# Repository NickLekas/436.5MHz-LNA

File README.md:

# 436.5MHz-LNA
A JFET common gate LNA for 436.5MHz

This is untested and may not work as designed.

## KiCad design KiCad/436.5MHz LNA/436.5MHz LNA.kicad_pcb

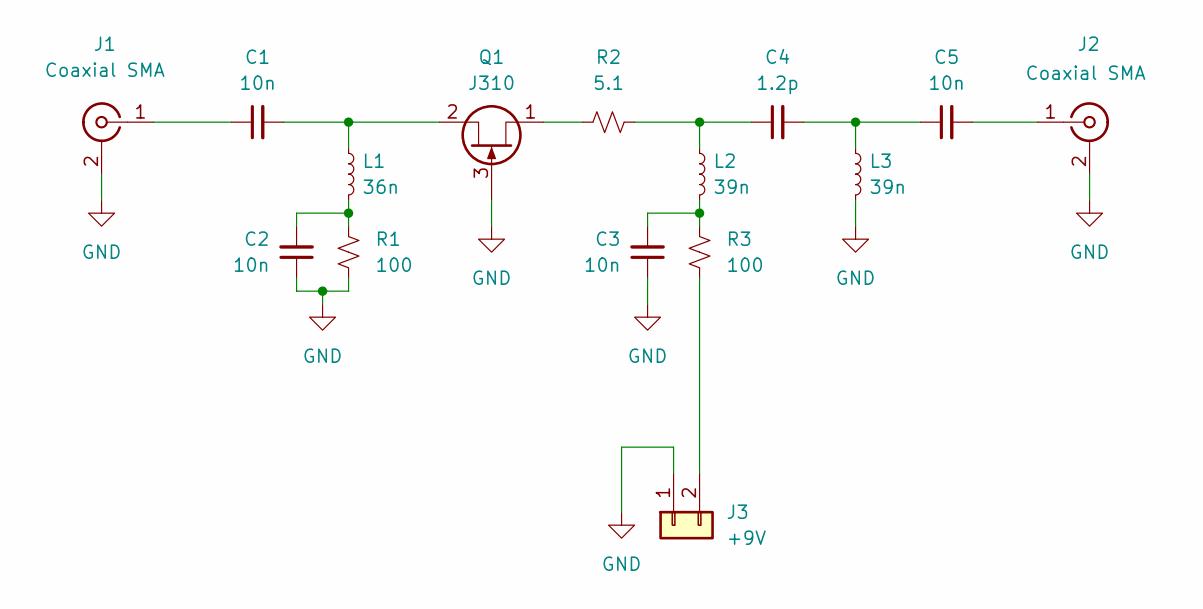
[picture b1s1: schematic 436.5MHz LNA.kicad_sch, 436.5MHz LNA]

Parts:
C1, C2, C3, C5: 10n; C_0603_1608Metric; MPN CL10C102JB8NNNC
C4: 1.2p; C_0603_1608Metric; MPN CC0603BRNPO9BN1R2‎
J1, J2: Coaxial SMA; SMA_Amphenol_132289_EdgeMount; MPN BU-1420701801
J3: +9V; PinHeader_1x02_P2.54mm_Vertical
L1: 36n; L_0603_1608Metric; MPN 0603DC-36NXJRW
L2, L3: 39n; L_0603_1608Metric; MPN 0603DC-39NXJRW
Q1: J310; SOT-23; MPN MMBFJ310LT3G
R1, R3: 100; R_0603_1608Metric; MPN CRGCQ0603F100R
R2: 5.1; R_0603_1608Metric; MPN RC0603FR-075R1L

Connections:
GND: C2.1, C3.1, J1.2 (Ext), J2.2 (Ext), J3.1, L3.2, Q1.3 (G), R1.2
unnamed: C1.1, J1.1 (In)
unnamed: C1.2, L1.1, Q1.2 (S)
unnamed: C2.2, L1.2, R1.1
unnamed: C3.2, L2.2, R3.1
unnamed: C4.1, L2.1, R2.2
unnamed: C4.2, C5.1, L3.1
unnamed: C5.2, J2.1 (In)
unnamed: J3.2, R3.2
unnamed: Q1.1 (D), R2.1

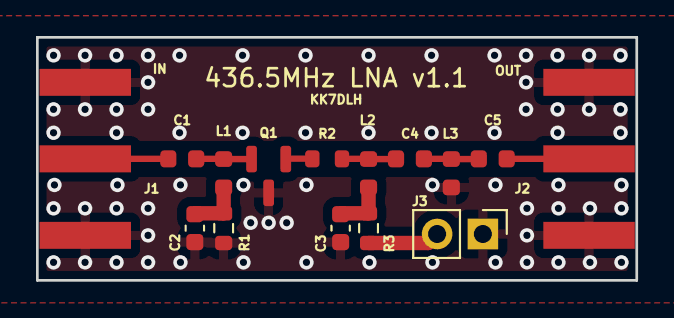
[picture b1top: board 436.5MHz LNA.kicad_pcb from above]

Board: 2 copper layers, 33.3 x 13.5 mm, 15 parts (0 on the bottom side), 10 nets.

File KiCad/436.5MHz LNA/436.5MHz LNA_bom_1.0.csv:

Quantity Per PCB,References,Value,MFN,MPN,Footprint,Dist,DPN,Datasheet
1,C4,1.2p,YAGEO,CC0603BRNPO9BN1R2‎,C_0603_1608Metric,DigiKey,311-3825-1-ND‎,~
4,C1 C2 C3 C5,10n,Samsung Electro-Mechanics,CL10C102JB8NNNC,C_0603_1608Metric,DigiKey,1276-1091-2-ND,~
1,J3,+9V,,,PinHeader_1x02_P2.54mm_Vertical,DigiKey,,~
2,J1 J2,Coaxial SMA,Muller Electric Co,BU-1420701801,SMA_Amphenol_132289_EdgeMount,DigiKey,314-1702-ND‎,https://www.muellerelectric.com/product_files/785/DS-BU-1420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
1,L1,36n,Coilcraft,0603DC-36NXJRW,L_0603_1608Metric,Coilcraft,0603DC-36NXJRW,https://www.coilcraft.com/getmedia/f3d98f97-cbe2-41fa-b3a9-5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
2,L2 L3,39n,Coilcraft,0603DC-39NXJRW,L_0603_1608Metric,Coilcraft,0603DC-39NXJRW,https://www.coilcraft.com/getmedia/f3d98f97-cbe2-41fa-b3a9-5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
1,Q1,J310,OnSemi,MMBFJ310LT3G,SOT-23,DigiKey,MMBFJ310LT3GOSCT-ND‎,https://www.farnell.com/datasheets/1796558.pdf
1,R2,5.1,YAGEO,RC0603FR-075R1L,R_0603_1608Metric,DigiKey,YAG3372CT-ND‎,~
2,R1 R3,100,TE Connectivity Passive Product,CRGCQ0603F100R,R_0603_1608Metric,DigiKey,A129676TR-ND,~





Component Groups:,9
Component Count:,15
Fitted Components:,15
Number of PCBs:,1
Total components:,15
Schematic Version:,1.0
Schematic Date:,
PCB Variant:,default
BoM Date:,3/8/2022 1:25:12 PM
Schematic Source:,436.5MHz LNA.kicad_sch
KiCad Version:,Eeschema (6.0.2)

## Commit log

2022-03-08 Create licence
2022-03-08 generated OSH Park fab files
2022-03-08 added BOM
2022-03-08 updated bom to purchase inductors from coilcraft and to remove most parts with terifs
2022-03-08 updated gitignore to remove backups
2022-03-18 no pushes from yesterday seem to have worked. Extended soldermask on rf path
2022-03-18 flipped the JFET so the gate has a more common ground with the RF path
